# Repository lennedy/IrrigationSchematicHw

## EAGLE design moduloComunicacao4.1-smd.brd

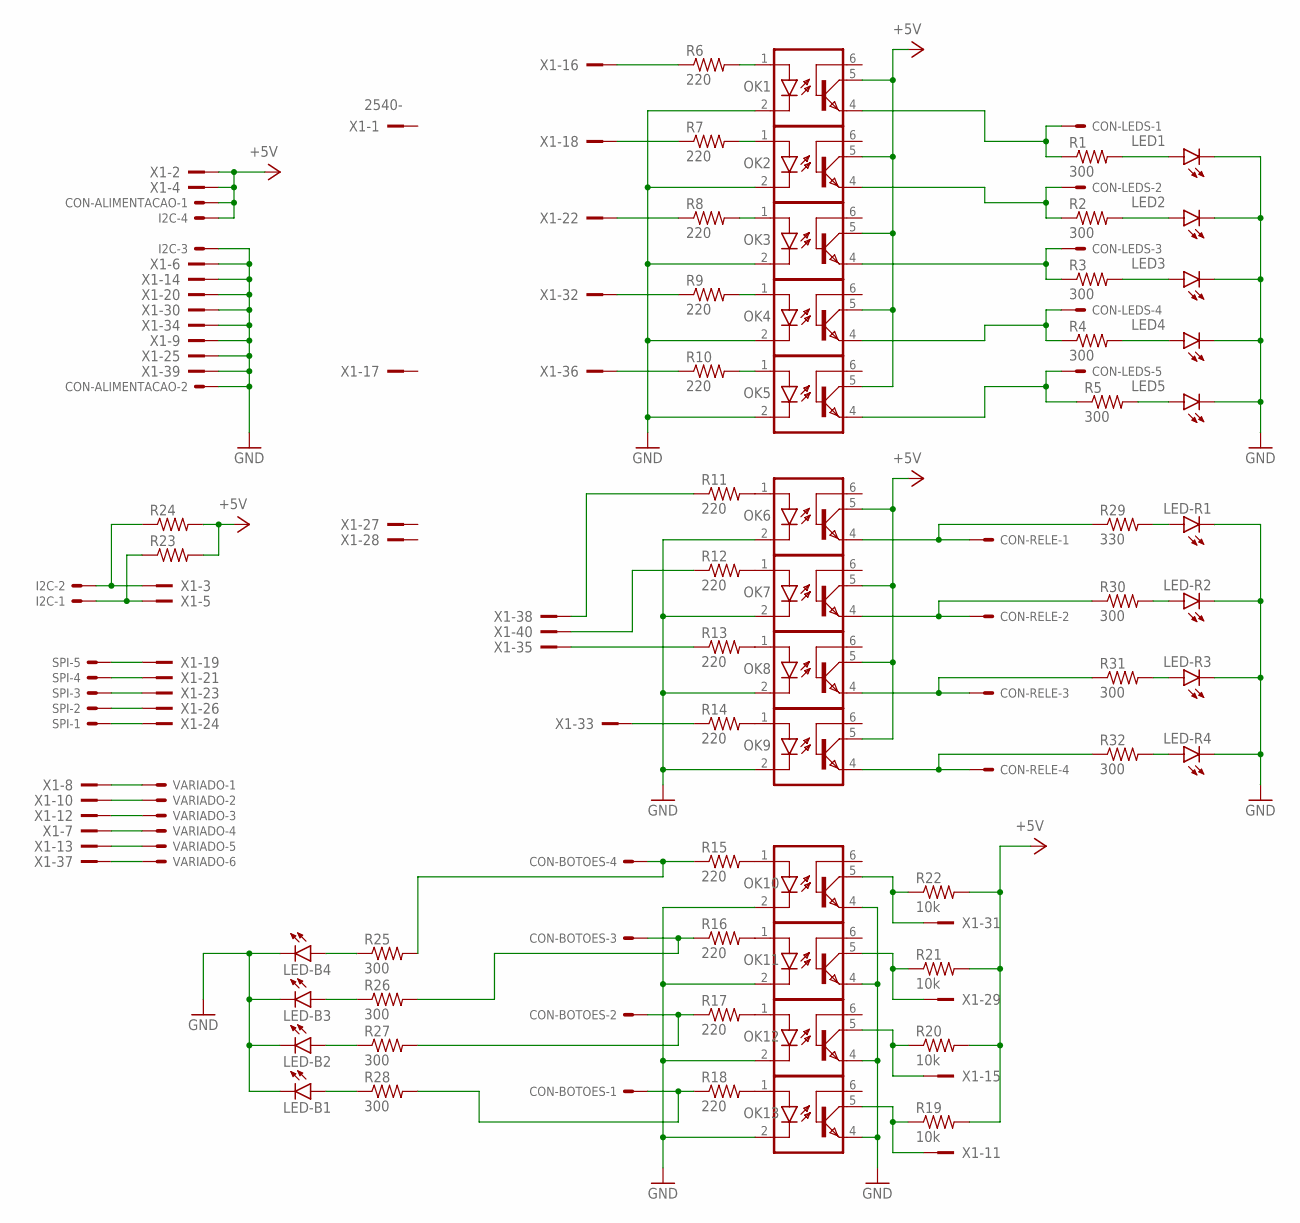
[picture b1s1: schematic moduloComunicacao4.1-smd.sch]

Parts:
CON-ALIMENTACAO: 22-23-2021
CON-BOTOES: 22-23-2041
CON-LEDS: 22-23-2051
CON-RELE: 22-23-2041
I2C: 22-23-2041
LED1, LED2, LED3, LED4, LED5: LED5MM
LED-B1, LED-B2, LED-B3, LED-B4: LEDCHIP-LED0805; CHIP-LED0805
LED-R1, LED-R2, LED-R3, LED-R4: LEDCHIP-LED0805; CHIP-LED0805
OK1, OK2, OK3, OK4, OK5, OK6, OK7, OK8, OK9, OK10, OK11, OK12, OK13: 4N25M; DIL06
R1, R2, R3, R4, R5: 300; 0207/12
R6, R7, R8, R9, R10, R11, R12, R13, R14: 220; 0204/7
R15, R16, R17, R18: 220; 0207/10
R19, R20, R21, R22: 10k; 0204/7
R23, R24: R-US_0204/5; 0204/5
R25, R26, R27, R28, R30, R31, R32: 300; R0805
R29: 330; R0805
SPI: 22-23-2051
VARIADO: 22-23-2061
X1: 2540-; PAK100/2500-40

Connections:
+5V: CON-ALIMENTACAO.1, I2C.4, OK1.5 (COL), OK2.5 (COL), OK3.5 (COL), OK4.5 (COL), OK5.5 (COL), OK6.5 (COL), OK7.5 (COL), OK8.5 (COL), OK9.5 (COL), R19.2, R20.2, R21.2, R22.2, R23.2, R24.2, X1.2, X1.4
GND: CON-ALIMENTACAO.2, I2C.3, LED1.K (C), LED2.K (C), LED3.K (C), LED4.K (C), LED5.K (C), LED-B1.C, LED-B2.C, LED-B3.C, LED-B4.C, LED-R1.C, LED-R2.C, LED-R3.C, LED-R4.C, OK1.2 (C), OK2.2 (C), OK3.2 (C), OK4.2 (C), OK5.2 (C), OK6.2 (C), OK7.2 (C), OK8.2 (C), OK9.2 (C), OK10.2 (C), OK10.4 (EMI), OK11.2 (C), OK11.4 (EMI), OK12.2 (C), OK12.4 (EMI), OK13.2 (C), OK13.4 (EMI), X1.6, X1.9, X1.14, X1.20, X1.25, X1.30, X1.34, X1.39
unnamed: LED1.A, R1.2
unnamed: LED2.A, R2.2
unnamed: LED3.A, R3.2
unnamed: LED4.A, R4.2
unnamed: LED5.A, R5.2
unnamed: CON-LEDS.1, OK1.4 (EMI), R1.1
unnamed: CON-LEDS.2, OK2.4 (EMI), R2.1
unnamed: CON-LEDS.3, OK3.4 (EMI), R3.1
unnamed: CON-LEDS.4, OK4.4 (EMI), R4.1
unnamed: CON-LEDS.5, OK5.4 (EMI), R5.1
unnamed: CON-RELE.1, OK6.4 (EMI), R29.1
unnamed: CON-RELE.2, OK7.4 (EMI), R30.1
unnamed: OK1.1 (A), R6.2
unnamed: OK2.1 (A), R7.2
unnamed: OK3.1 (A), R8.2
unnamed: OK4.1 (A), R9.2
unnamed: OK5.1 (A), R10.2
unnamed: CON-RELE.3, OK8.4 (EMI), R31.1
unnamed: CON-RELE.4, OK9.4 (EMI), R32.1
unnamed: OK6.1 (A), R11.2
unnamed: OK7.1 (A), R12.2
unnamed: OK8.1 (A), R13.2
unnamed: OK9.1 (A), R14.2
unnamed: OK10.1 (A), R15.2
unnamed: OK11.1 (A), R16.2
unnamed: OK12.1 (A), R17.2
unnamed: OK13.1 (A), R18.2
unnamed: CON-BOTOES.4, R15.1, R25.2
unnamed: CON-BOTOES.2, R17.1, R27.2
unnamed: CON-BOTOES.3, R16.1, R26.2
unnamed: CON-BOTOES.1, R18.1, R28.2
unnamed: OK13.5 (COL), R19.1, X1.11
unnamed: R13.1, X1.35
unnamed: OK12.5 (COL), R20.1, X1.15
unnamed: R12.1, X1.40
unnamed: OK11.5 (COL), R21.1, X1.29
unnamed: R14.1, X1.33
unnamed: OK10.5 (COL), R22.1, X1.31
unnamed: R11.1, X1.38
unnamed: R6.1, X1.16
unnamed: R7.1, X1.18
unnamed: R8.1, X1.22
unnamed: R9.1, X1.32
unnamed: R10.1, X1.36
unnamed: I2C.2, R24.1, X1.3
unnamed: I2C.1, R23.1, X1.5
unnamed: SPI.5, X1.19
unnamed: SPI.4, X1.21
unnamed: SPI.3, X1.23
unnamed: SPI.2, X1.26
unnamed: SPI.1, X1.24
unnamed: VARIADO.3, X1.12
unnamed: VARIADO.2, X1.10
unnamed: VARIADO.1, X1.8
unnamed: VARIADO.4, X1.7
unnamed: VARIADO.5, X1.13
unnamed: VARIADO.6, X1.37
unnamed: LED-B4.A, R25.1
unnamed: LED-B3.A, R26.1
unnamed: LED-B2.A, R27.1
unnamed: LED-B1.A, R28.1
unnamed: LED-R4.A, R32.2
unnamed: LED-R3.A, R31.2
unnamed: LED-R2.A, R30.2
unnamed: LED-R1.A, R29.2

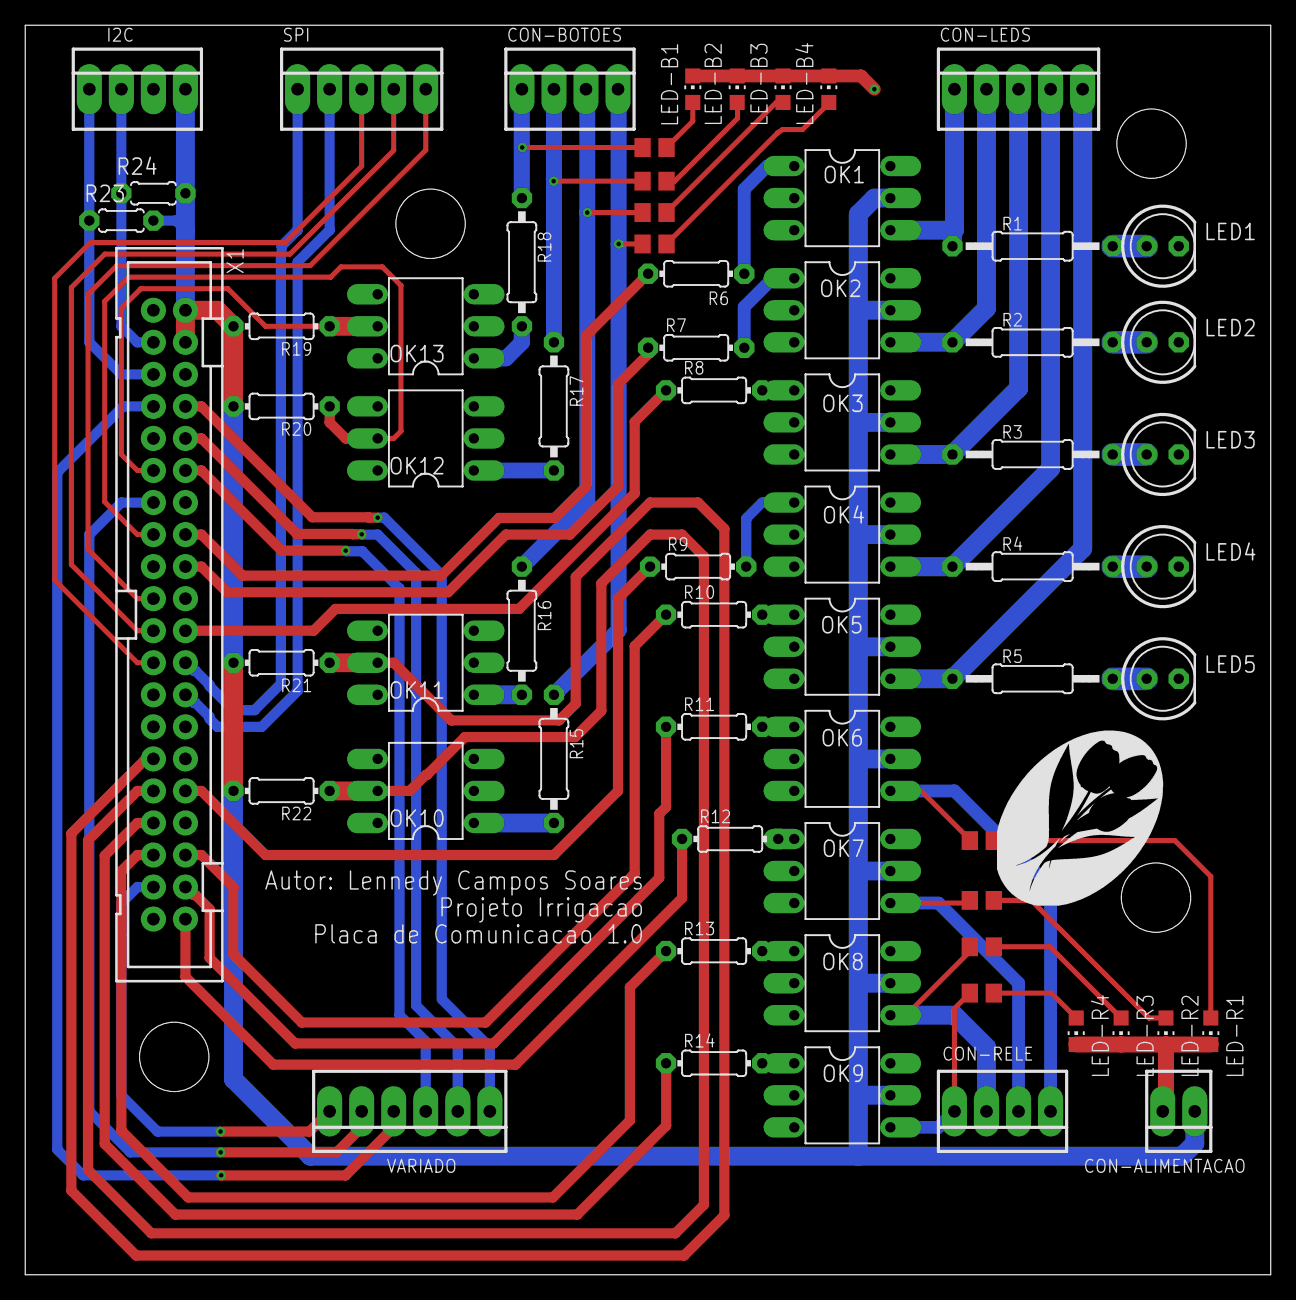
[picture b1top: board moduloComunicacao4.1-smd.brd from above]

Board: 2 copper layers, 98.7 x 99.1 mm, 66 parts (0 on the bottom side), 67 nets.

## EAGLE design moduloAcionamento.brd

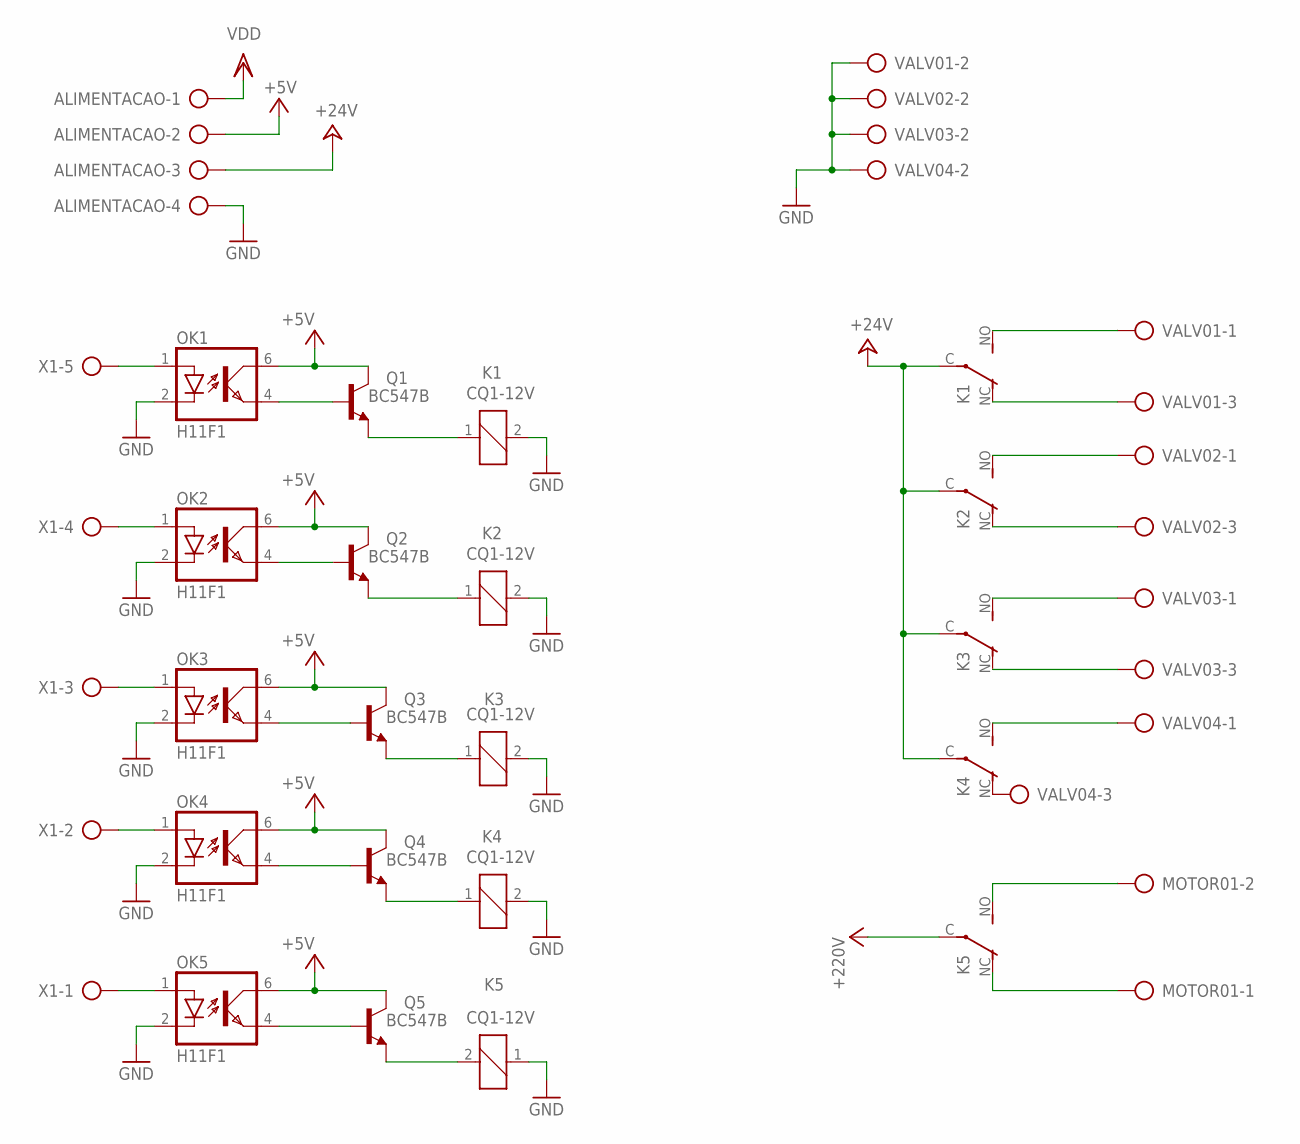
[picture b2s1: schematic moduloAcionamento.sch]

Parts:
ALIMENTACAO: AK500/4
K1, K2, K3, K4, K5: CQ1-12V; CQ1
MOTOR01: AK500/2
OK1, OK2, OK3, OK4, OK5: H11F1; DIL05
Q1, Q2, Q3, Q4, Q5: BC547B; TO92
VALV01, VALV02, VALV03, VALV04: AK500/3
X1: AK500/5

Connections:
+5V: ALIMENTACAO.2, K5.C, OK1.6 (COL), OK2.6 (COL), OK3.6 (COL), OK4.6 (COL), OK5.6 (COL), Q1.3 (C), Q2.3 (C), Q3.3 (C), Q4.3 (C), Q5.3 (C)
+24V: ALIMENTACAO.3, K1.C, K2.C, K3.C, K4.C
GND: ALIMENTACAO.4, K1.2, K2.2, K3.2, K4.2, K5.1, OK1.2 (C), OK2.2 (C), OK3.2 (C), OK4.2 (C), OK5.2 (C), VALV01.2, VALV02.2, VALV03.2, VALV04.2
unnamed: OK4.4 (EMIT), Q4.2 (B)
unnamed: K4.1, Q4.1 (E)
unnamed: K3.1, Q3.1 (E)
unnamed: OK3.4 (EMIT), Q3.2 (B)
unnamed: K1.1, Q1.1 (E)
unnamed: K2.1, Q2.1 (E)
unnamed: OK2.4 (EMIT), Q2.2 (B)
unnamed: OK5.4 (EMIT), Q5.2 (B)
unnamed: OK5.1 (A), X1.1
unnamed: K5.2, Q5.1 (E)
unnamed: OK1.4 (EMIT), Q1.2 (B)
unnamed: OK4.1 (A), X1.2
unnamed: OK3.1 (A), X1.3
unnamed: OK2.1 (A), X1.4
unnamed: OK1.1 (A), X1.5
unnamed: K1.NC (O), VALV01.3
unnamed: K1.NO (S), VALV01.1
unnamed: K2.NO (S), VALV02.1
unnamed: K2.NC (O), VALV02.3
unnamed: K3.NO (S), VALV03.1
unnamed: K3.NC (O), VALV03.3
unnamed: K4.NO (S), VALV04.1
unnamed: K4.NC (O), VALV04.3
unnamed: K5.NO (S), MOTOR01.2
unnamed: K5.NC (O), MOTOR01.1
VDD: ALIMENTACAO.1

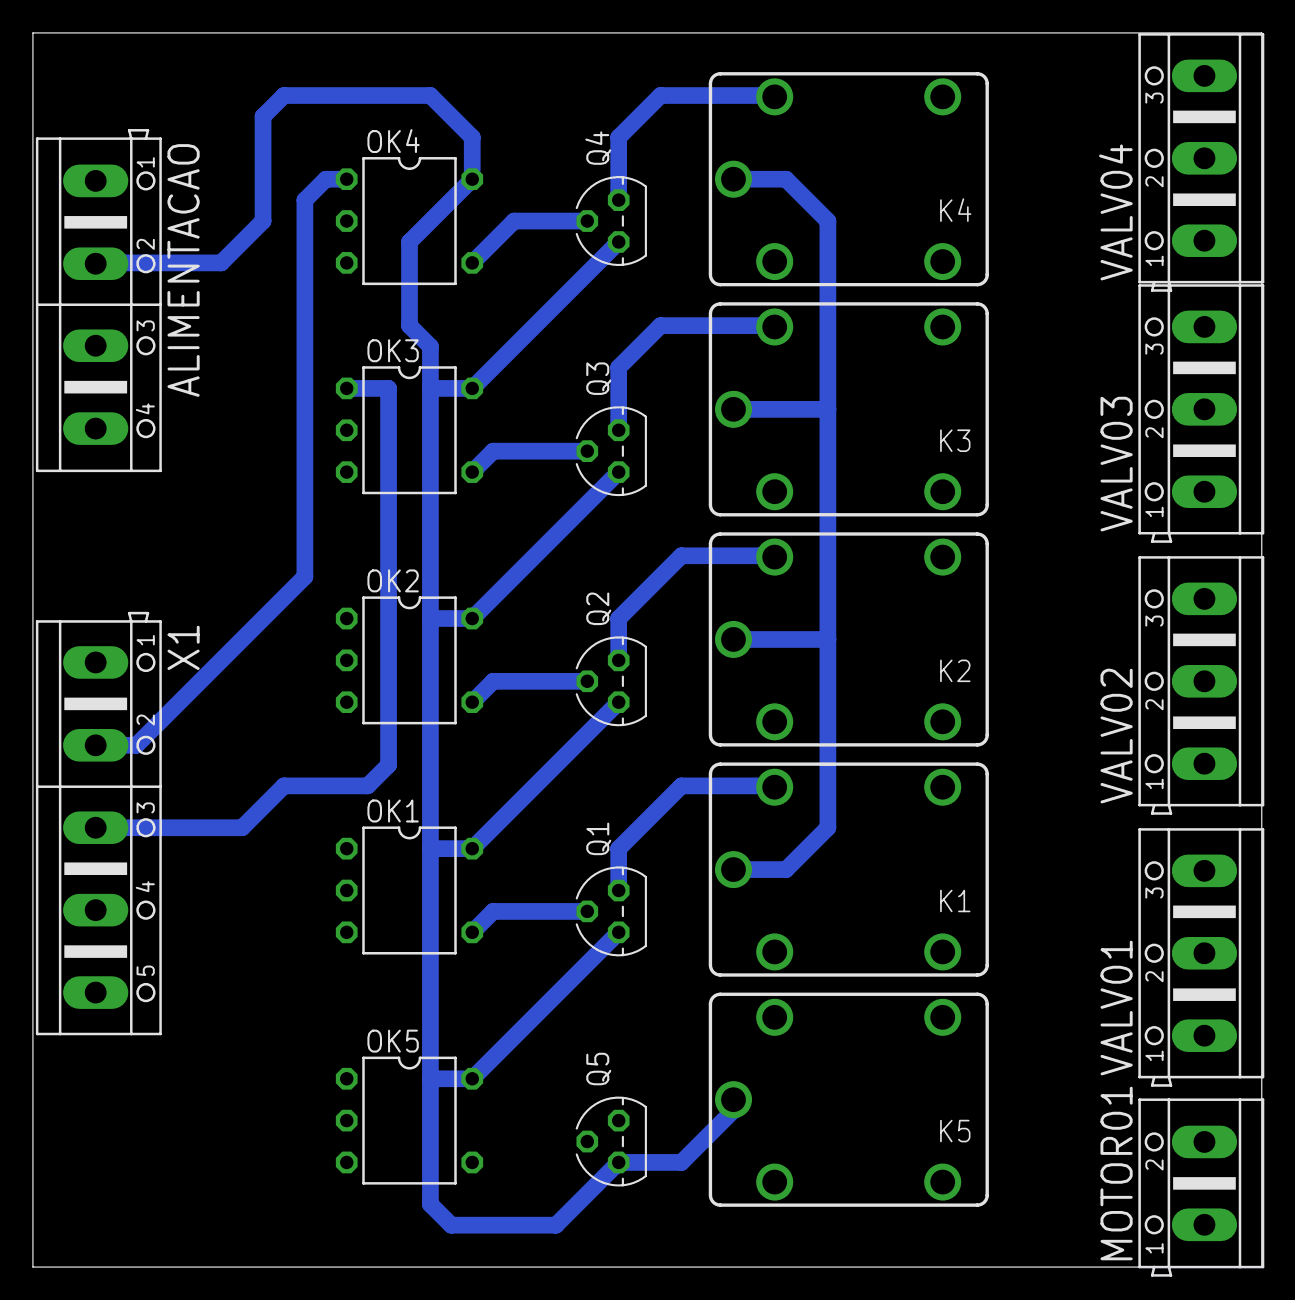
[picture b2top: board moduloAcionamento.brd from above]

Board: 2 copper layers, 74.6 x 74.9 mm, 22 parts (0 on the bottom side), 28 nets.

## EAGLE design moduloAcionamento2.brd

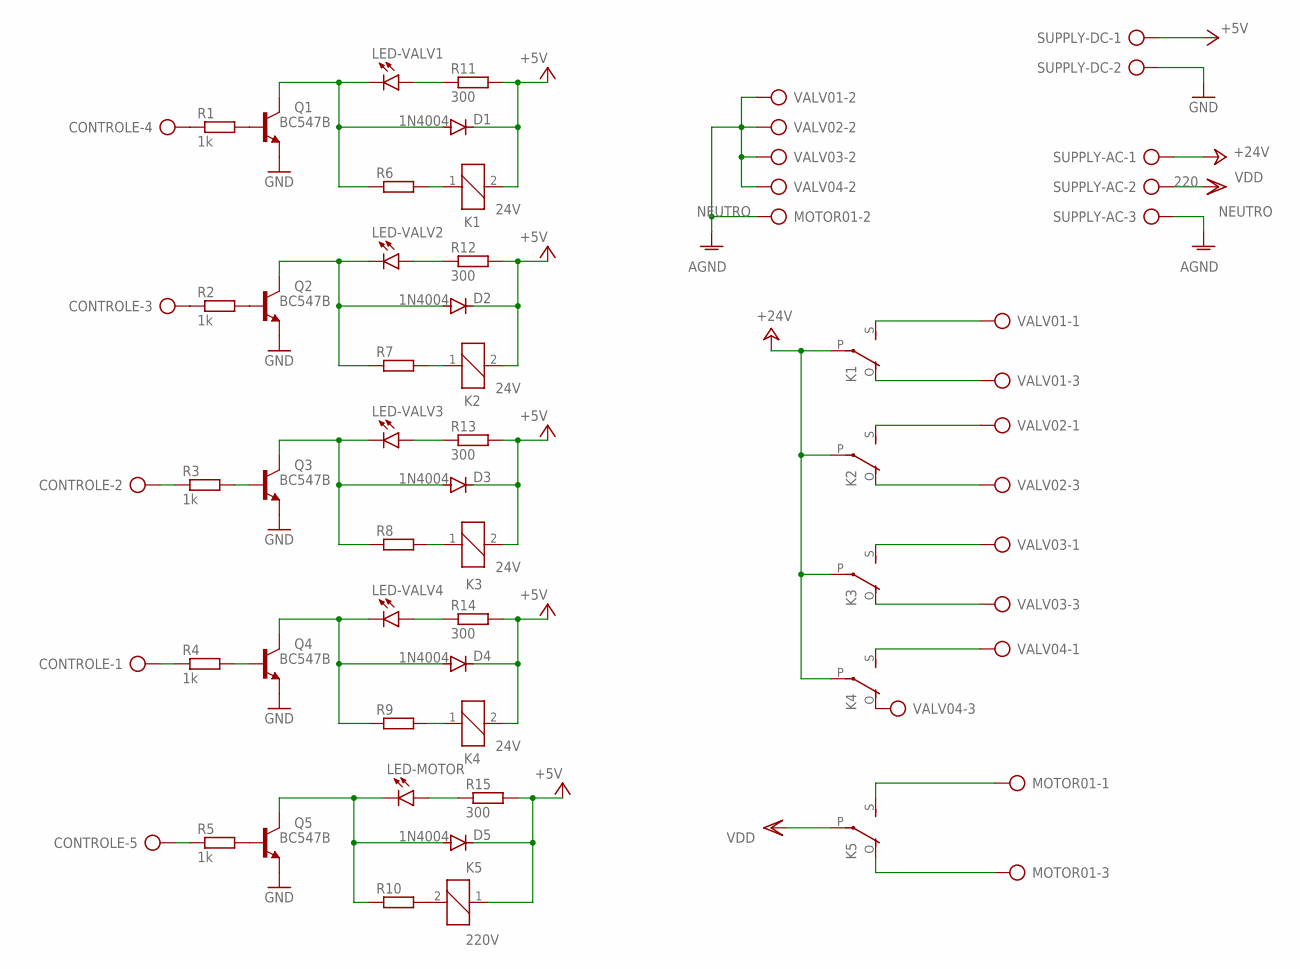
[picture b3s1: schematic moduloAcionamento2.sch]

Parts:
CONTROLE: AK500/5
D1, D2, D3, D4, D5: 1N4004; DO41-10
K1, K2, K3, K4: 24V; G5LE
K5: 220V; G5LE
LED-MOTOR: LED5MM
LED-VALV1, LED-VALV2, LED-VALV3, LED-VALV4: LED5MM
MOTOR01: AK500/3
Q1, Q2, Q3, Q4, Q5: BC547B; TO92
R1, R2, R3, R4, R5: 1k; 0204/7
R6, R7, R8, R9, R10: R-EU_0204/7; 0204/7
R11, R12, R13, R14, R15: 300; 0204/7
SUPPLY-AC: AK500/3
SUPPLY-DC: AK500/2
VALV01, VALV02, VALV03, VALV04: AK500/3

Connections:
220: K5.P, SUPPLY-AC.2
+5V: D1.C, D2.C, D3.C, D4.C, D5.C, K1.2, K2.2, K3.2, K4.2, K5.1, R11.2, R12.2, R13.2, R14.2, R15.2, SUPPLY-DC.1
+24V: K1.P, K2.P, K3.P, K4.P, SUPPLY-AC.1
GND: Q1.1 (E), Q2.1 (E), Q3.1 (E), Q4.1 (E), Q5.1 (E), SUPPLY-DC.2
unnamed: Q1.2 (B), R1.2
unnamed: K1.1, R6.2
unnamed: D2.A, LED-VALV2.K (C), Q2.3 (C), R7.1
unnamed: CONTROLE.4, R1.1
unnamed: K3.1, R8.2
unnamed: LED-VALV1.A, R11.1
unnamed: CONTROLE.3, R2.1
unnamed: Q2.2 (B), R2.2
unnamed: Q3.2 (B), R3.2
unnamed: D4.A, LED-VALV4.K (C), Q4.3 (C), R9.1
unnamed: CONTROLE.2, R3.1
unnamed: CONTROLE.1, R4.1
unnamed: Q4.2 (B), R4.2
unnamed: CONTROLE.5, R5.1
unnamed: Q5.2 (B), R5.2
unnamed: K1.O, VALV01.3
unnamed: K1.S, VALV01.1
unnamed: K2.S, VALV02.1
unnamed: K2.O, VALV02.3
unnamed: K3.S, VALV03.1
unnamed: K3.O, VALV03.3
unnamed: K4.S, VALV04.1
unnamed: K4.O, VALV04.3
unnamed: K5.S, MOTOR01.1
unnamed: LED-VALV2.A, R12.1
unnamed: K2.1, R7.2
unnamed: K4.1, R9.2
unnamed: D5.A, LED-MOTOR.K (C), Q5.3 (C), R10.1
unnamed: K5.2, R10.2
unnamed: LED-VALV3.A, R13.1
unnamed: LED-VALV4.A, R14.1
unnamed: D1.A, LED-VALV1.K (C), Q1.3 (C), R6.1
unnamed: D3.A, LED-VALV3.K (C), Q3.3 (C), R8.1
unnamed: LED-MOTOR.A, R15.1
unnamed: K5.O, MOTOR01.3
NEUTRO: MOTOR01.2, SUPPLY-AC.3, VALV01.2, VALV02.2, VALV03.2, VALV04.2

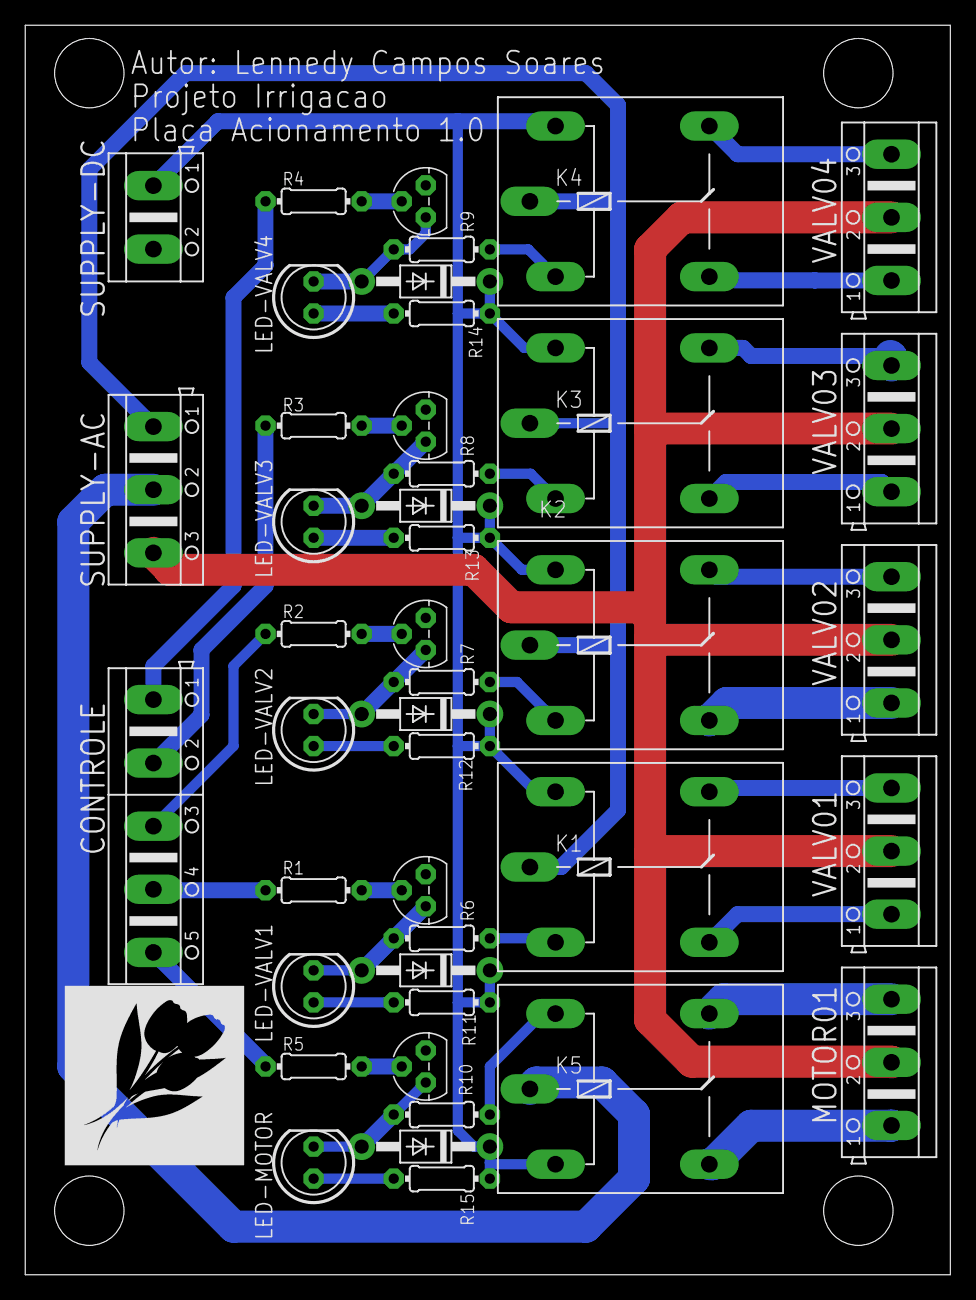
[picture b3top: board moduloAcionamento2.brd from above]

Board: 2 copper layers, 73.3 x 99.1 mm, 43 parts (0 on the bottom side), 40 nets.

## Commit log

2021-05-21 criação de repositorio para armazenar informações da placa de controle
